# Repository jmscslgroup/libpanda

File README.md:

# Interface library for comma.ai's USB panda.

A library that handles communication with a comma.ai Panda interface device.  Simple demos collect data from the panda (grey version) to the screen.

A tutorial for hardware setup is located here:
[https://jmscslgroup.github.io/libpanda/](https://jmscslgroup.github.io/libpanda/)

Full Raspbian-based images with ROS/libpanda preinstalled can be found here:
[https://jmscslgroup.github.io/libpanda/doc/image.md](doc/image.md)

## Dependencies:
1. Required - libusb-1.0-0-dev
2. Optional - libcurses5-dev
3. Included - NMEAParser from https://github.com/visualgps/NMEAParser/

### libusb-1.0-0-dev
The core of this library is based on libusb, the default version installable through Ubuntu's apt-get.

### libcurses5-dev
An optional example for data visualization is based on ncurses.  If desired to run this example, libcurses needs to be installed but is not required

### NMEAParser
The NMEAParser is already included as a modified version with some bug fixes and added features.
1. Bugs fixed:
* Incomplete time precision for seconds in RMC strings
* Year calculation incorrect byte offset resulting in incorrect year parsings
2. Additional features:
* ZDA NMEA message parsing

## Setup:
These instructions were successful on a Raspberry pi 4 running Ubuntu 18.04.
### Install libusb-1.0-0-dev
`$ sudo apt-get install libusb-1.0-0-dev`

### Optional: install libsurses5-dev
`$ sudo apt-get install libncurses5-dev`

### Compile
1. `$ mkdir build`
2. `$ cd build`
3. `$ cmake ..`
4. `$ make`

## Examples
### simplecan
Minimal example showing a minimal implementation of classes Panda::Usb and Panda::Can (no GPS).

`$ sudo ./simplecan`

### simplegps
Minimal example showing a minimal implementation of classes Panda::Usb and Panda::Gps (no CAN).

`$ sudo ./simplegps`

### panda
Barebones example showing a minimal implementation of class Panda::Handler, utilizing Panda::Usb, Panda::Can, and Panda::Gps.  Command line arguments can be specified to record log files.

Simple Execution:

`$ sudo ./panda`

Saving CSV CAN data to file:

`$ sudo ./panda -c csvData.txt`

Saving GPS NMEA data to file, and also run USB in synchronous mode:

`$ sudo ./panda -u s -g nmeaStrings.txt`

Saving GPS NMEA, CSV CAN, and raw CAN data simultaneously:

`$ sudo ./panda -c csvData.txt -g nmeaStrings.txt -r rawCANdata.txt`

### pandaSetTime
This example listens to the GPS and when data is valid, synchronizes the system clock to the GPS's UTC if the difference is larger than a defined delta.

`$ sudo ./pandaSetTime`

### pandaCurses
An example that plots GPS and CAN data to the console in a pretty fashion.  This also takes arguments for various data collection and hardware modes.

`$ sudo ./pandaCurses`

Save NMEA strings to a file named nmeaFile.txt:

`$ sudo ./pandaCurses -g nmeaFile.txt`

Run with USB in synchronous mode (default is asynchronous):

`$ sudo ./pandaCurses -u s`

Run with faked CAN data (i.e. when not connected to a car...):

`$ sudo ./pandaCurses -f`

## Documentation:
The library is self-documenting using Doxygen, producing both HTML and LaTex.  Generate the documentation as follows:

`$ doxygen doxygen.conf`

If you do not have doxyen, you may install using, on Ubuntu:

`$ sudo apt-get install doxygen`

Or on macOS with macports:

`$ sudo port install doxygen`

## Todo
- [x] Panda GPS interface
- [ ] Isochronous USB transfer
- [ ] Timestamped libusb error logging
- [x] CAN frame parsing
- [x] CAN frame handling
- [ ] ROS based publishing
- [ ] Testing

# LICENSE

> Author: Matt Bunting
> Copyright (c) 2021 Arizona Board of Regents
> All rights reserved.
> Permission is hereby granted, without written agreement and without
> license or royalty fees, to use, copy, modify, and distribute this
> software and its documentation for any purpose, provided that the
> above copyright notice and the following two paragraphs appear in
> all copies of this software.

> IN NO EVENT SHALL THE ARIZONA BOARD OF REGENTS BE LIABLE TO ANY PARTY
> FOR DIRECT, INDIRECT, SPECIAL, INCIDENTAL, OR CONSEQUENTIAL DAMAGES
> ARISING OUT OF THE USE OF THIS SOFTWARE AND ITS DOCUMENTATION, EVEN
> IF THE UNIVERSITY OF CALIFORNIA HAS BEEN ADVISED OF THE POSSIBILITY OF
> SUCH DAMAGE.
> THE ARIZONA BOARD OF REGENTS SPECIFICALLY DISCLAIMS ANY WARRANTIES,
> INCLUDING, BUT NOT LIMITED TO, THE IMPLIED WARRANTIES OF MERCHANTABILITY
> AND FITNESS FOR A PARTICULAR PURPOSE. THE SOFTWARE PROVIDED HEREUNDER
> IS ON AN "AS IS" BASIS, AND THE UNIVERSITY OF CALIFORNIA HAS NO OBLIGATION
> TO PROVIDE MAINTENANCE, SUPPORT, UPDATES, ENHANCEMENTS, OR MODIFICATIONS.

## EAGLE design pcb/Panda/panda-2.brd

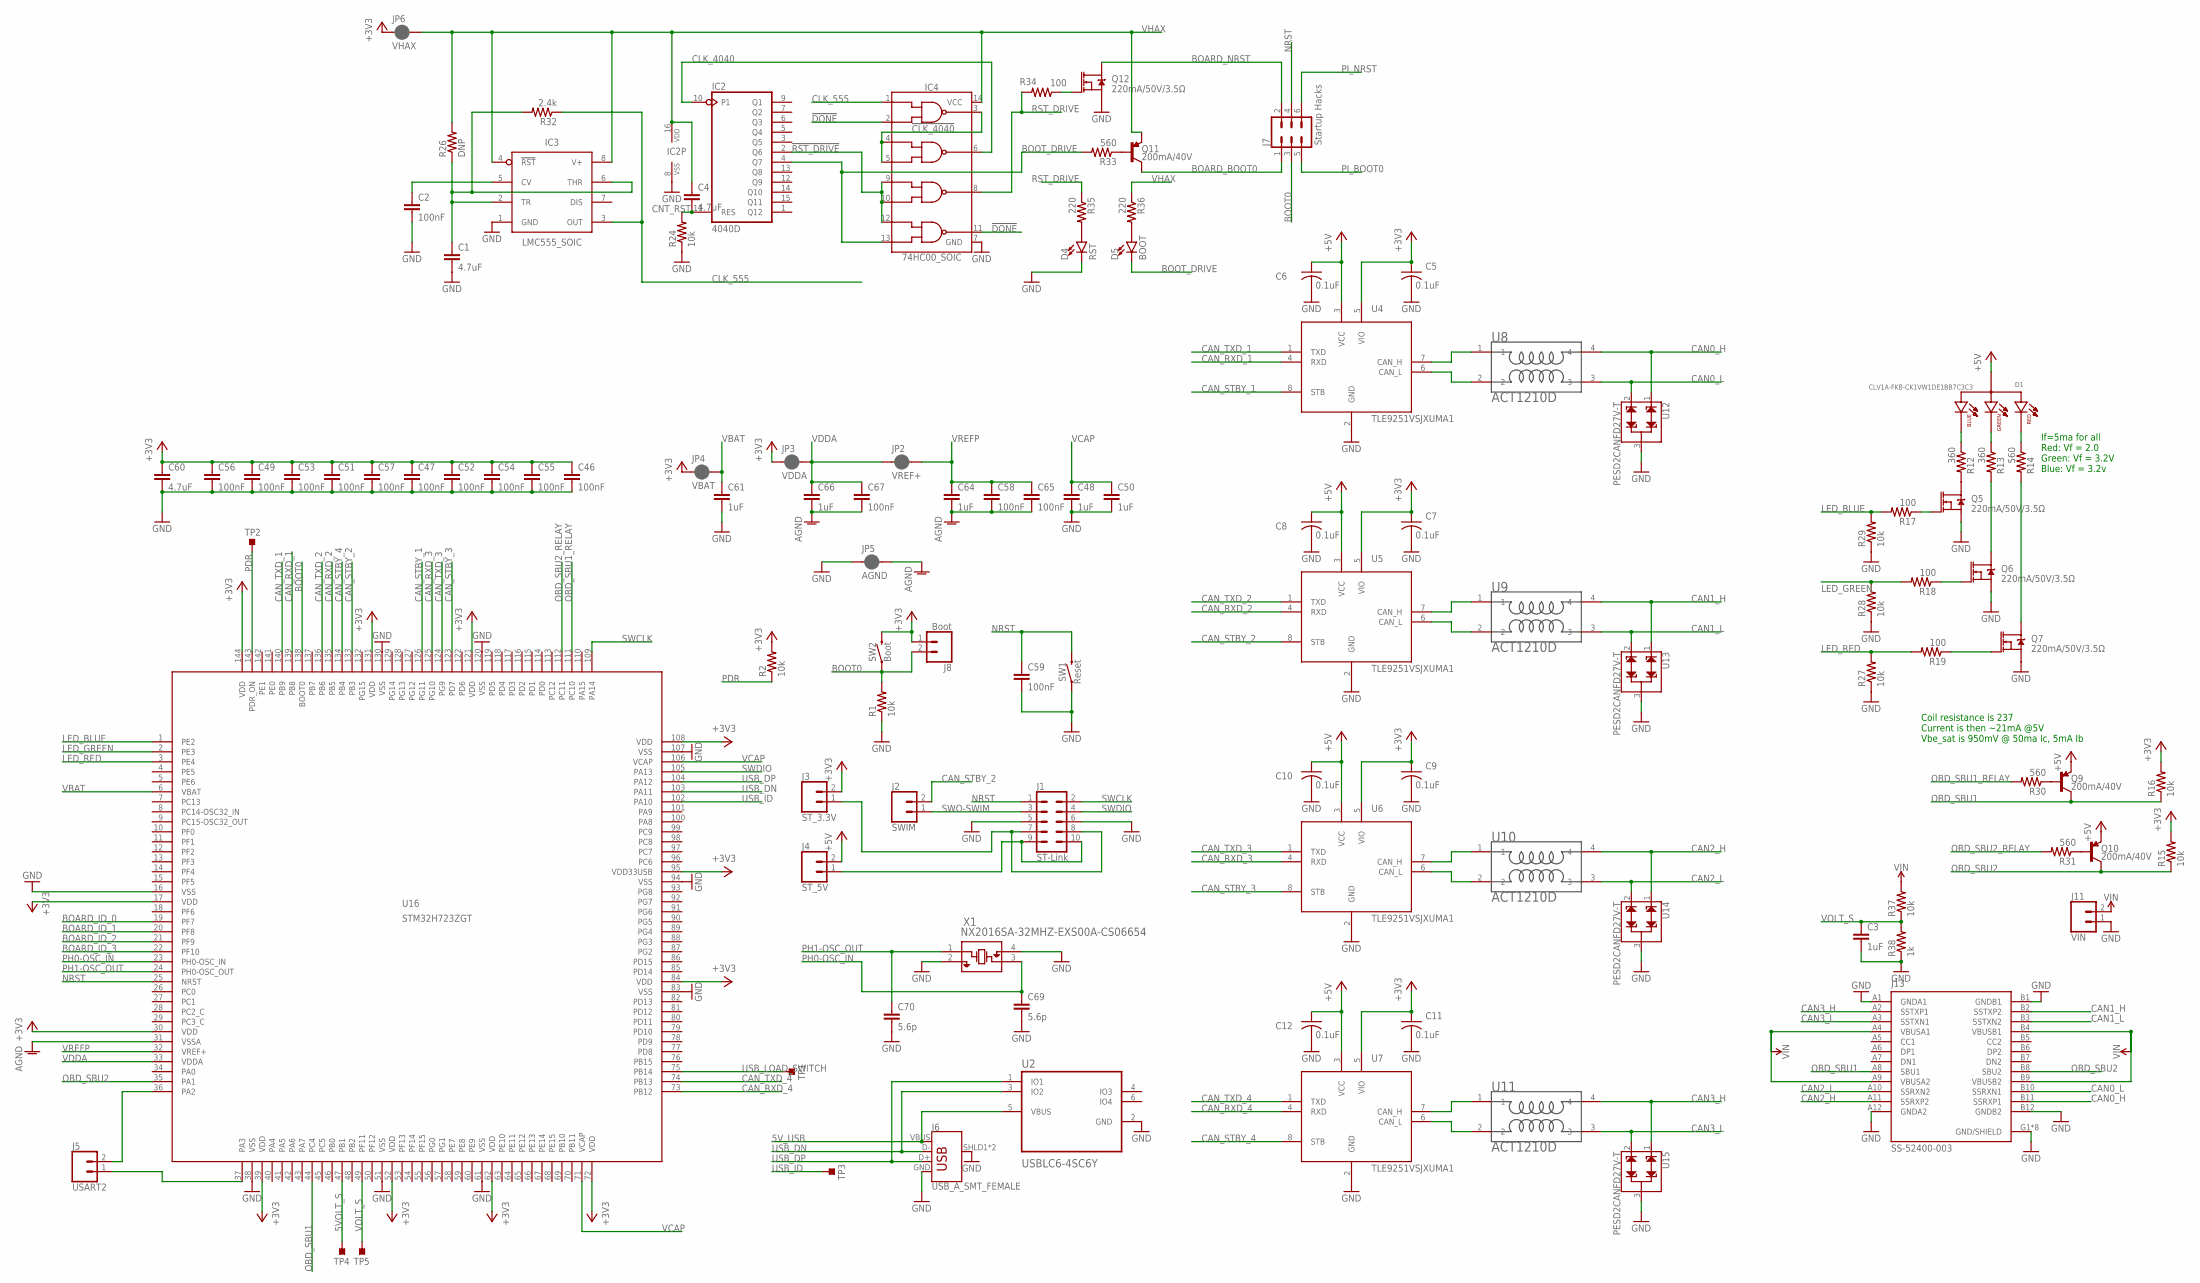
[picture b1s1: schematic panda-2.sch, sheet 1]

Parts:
C1, C4, C60: 4.7uF; C0603
C2, C46, C47, C49, C51, C52, C53, C54, C55, C56, C57, C58, C59, C65, C67: 100nF; C0402
C3, C48, C50, C61, C64, C66: 1uF; C0402
C5, C6, C7, C8, C9, C10, C11, C12: 0.1uF; C0402
C69, C70: 5.6p; C0402
D1: CLV1A-FKB-CK1VW1DE1BB7C3C3; LED_CLV1A-FKB-CK1VW1DE1BB7C3C3
D4: RST; LED-0603
D5: BOOT; LED-0603
IC2: 4040D; SO16
IC3: LMC555_SOIC; SOIC127P599X175-8N
IC4: 74HC00_SOIC; SOIC127P600X175-14N
J1: ST-Link; 2X5-SHROUDED-NS
J2: SWIM; 1X02
J3: ST_3.3V; 1X02
J4: ST_5V; 1X02
J5: USART2; 1X02
J6: USB_A_SMT_FEMALE; USB-A-S-SILK-FEMALE
J7: Startup Hacks; 2X3
J8: Boot; 1X02
J11: VIN; 1X02
J13: SS-52400-003; BELFUSE_SS-52400-003
JP2: VREF+; SMT-JUMPER_2_NC_PASTE_SILK
JP3: VDDA; SMT-JUMPER_2_NC_PASTE_SILK
JP4: VBAT; SMT-JUMPER_2_NC_PASTE_SILK
JP5: AGND; SMT-JUMPER_2_NC_PASTE_SILK
JP6: VHAX; SMT-JUMPER_2_NC_PASTE_SILK
Q5, Q6, Q7, Q12: 220mA/50V/3.5Ω; SOT23-3
Q9, Q10, Q11: 200mA/40V; SOT23-3
R1, R2, R15, R16, R24, R27, R28, R29, R37: 10k; R0402
R12, R13: 360; R0402
R14, R30, R31, R33: 560; R0402
R17, R18, R19, R34: 100; R0402
R26: DNP; R0402
R32: 2.4k; R0402
R35, R36: 220; R0402
R38: 1k; R0402
SW1: Reset; TACTILE_SWITCH_PTH_6.0MM
SW2: Boot; TACTILE_SWITCH_PTH_6.0MM
TP1: USB_LOAD_SWITCH; TESTPOINT_SMD-10SN
TP2: PDR_ON; TESTPOINT_SMD-10SN
TP3: USB_ID; TESTPOINT_SMD-10SN
TP4: 5VOUT_S; TESTPOINT_SMD-10SN
TP5: VOLT_S; TESTPOINT_SMD-10SN
U2: USBLC6-4SC6Y; SOT95P280X145-6N
U4, U5, U6, U7: TLE9251VSJXUMA1; SOIC8
U8, U9, U10, U11: ACT1210D; ACT1210-101-2P-TL
U12, U13, U14, U15: PESD2CANFD27V-T; DBZ_R-PDSO-G3
U16: STM32H723ZGT; LQFP-144
X1: NX2016SA-32MHZ-EXS00A-CS06654; NX2016SA_NDK

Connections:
5VOLT_S: TP4.TP, U16.47 (PB1)
5V_USB: J6.VBUS, U2.5 (VBUS); also elsewhere on the board
!CLK_4040: IC4.3 (1Y), IC4.4 (2A), IC4.5 (2B)
!DONE: IC4.2 (1B), IC4.11 (4Y)
!RST_DRIVE: IC2.2 (Q6), IC4.9 (3A), IC4.10 (3B), IC4.12 (4A)
+3V3: C5.1, C7.1, C9.1, C11.1, C46.1, C47.1, C49.1, C51.1, C52.1, C53.1, C54.1, C55.1, C56.1, C57.1, C60.1, J3.2, J8.1, JP3.1, JP4.1, JP6.1, R2.2, R15.2, R16.2, SW2.3 (2), U4.5 (VIO), U5.5 (VIO), U6.5 (VIO), U7.5 (VIO), U16.17 (VDD), U16.30 (VDD), U16.39 (VDD), U16.52 (VDD), U16.62 (VDD), U16.72 (VDD), U16.84 (VDD), U16.95 (VDD33USB), U16.108 (VDD), U16.121 (VDD), U16.131 (VDD), U16.144 (VDD); also elsewhere on the board
+5V: C6.1, C8.1, C10.1, C12.1, D1.2 (A), J4.2, Q9.2 (E), Q10.2 (E), U4.3 (VCC), U5.3 (VCC), U6.3 (VCC), U7.3 (VCC); also elsewhere on the board
AGND: C58.2, C64.2, C65.2, C66.2, C67.2, JP5.2, U16.31 (VSSA)
BOARD_BOOT0: J7.1, Q11.3 (C)
BOARD_ID_0: U16.19 (PF7)
BOARD_ID_1: U16.20 (PF8)
BOARD_ID_2: U16.21 (PF9)
BOARD_ID_3: U16.22 (PF10)
BOARD_NRST: J7.2, Q12.3 (D)
BOOT0: J7.3, J8.2, R1.2, SW2.1, U16.138 (BOOT0)
BOOT_DRIVE: D5.C, IC2.4 (Q7), IC4.13 (4B), R33.2
CAN0_H: J13.B11 (SSRXP1), U8.4, U12.1
CAN0_L: J13.B10 (SSRXN1), U8.3, U12.2
CAN1_H: J13.B2 (SSTXP2), U9.4, U13.1
CAN1_L: J13.B3 (SSTXN2), U9.3, U13.2
CAN2_H: J13.A11 (SSRXP2), U10.4, U14.1
CAN2_L: J13.A10 (SSRXN2), U10.3, U14.2
CAN3_H: J13.A2 (SSTXP1), U11.4, U15.1
CAN3_L: J13.A3 (SSTXN1), U11.3, U15.2
CAN_RXD_1: U4.4 (RXD), U16.139 (PB8)
CAN_RXD_2: U5.4 (RXD), U16.135 (PB5)
CAN_RXD_3: U6.4 (RXD), U16.125 (PG10)
CAN_RXD_4: U7.4 (RXD), U16.73 (PB12)
CAN_STBY_1: U4.8 (STB), U16.126 (PG11)
CAN_STBY_2: J2.2, U5.8 (STB), U16.133 (PB3)
CAN_STBY_3: U6.8 (STB), U16.123 (PD7)
CAN_STBY_4: U7.8 (STB), U16.134 (PB4)
CAN_TXD_1: U4.1 (TXD), U16.140 (PB9)
CAN_TXD_2: U5.1 (TXD), U16.136 (PB6)
CAN_TXD_3: U6.1 (TXD), U16.124 (PG9)
CAN_TXD_4: U7.1 (TXD), U16.74 (PB13)
CLK_555: IC3.3 (OUT), IC4.1 (1A), R32.1
CLK_4040: IC2.10 (P1), IC4.6 (2Y)
CNT_RST: C4.2, IC2.11 (RES), R24.2
GND: C1.2, C2.2, C3.2, C5.2, C6.2, C7.2, C8.2, C9.2, C10.2, C11.2, C12.2, C46.2, C47.2, C48.2, C49.2, C50.2, C51.2, C52.2, C53.2, C54.2, C55.2, C56.2, C57.2, C59.2, C60.2, C61.2, C69.2, C70.2, D4.C, IC2.8 (VSS), IC3.1 (GND), IC4.7 (GND), J1.5, J1.6, J6.GND, J6.SHLD1 (SHIELD), J6.SHLD2 (SHIELD), J11.1, J13.A1 (GNDA1), J13.A12 (GNDA2), J13.B1 (GNDB1), J13.B12 (GNDB2), J13.G1 (GND/SHIELD), J13.G2 (GND/SHIELD), J13.G3 (GND/SHIELD), J13.G4 (GND/SHIELD), J13.S1 (GND/SHIELD), J13.S2 (GND/SHIELD), J13.S3 (GND/SHIELD), J13.S4 (GND/SHIELD), JP5.1, Q5.2 (S), Q6.2 (S), Q7.2 (S), Q12.2 (S), R1.1, R24.1, R27.1, R28.1, R29.1, R38.1, SW1.1, U2.2 (GND), U4.2 (GND), U5.2 (GND), U6.2 (GND), U7.2 (GND), U12.3, U13.3, U14.3, U15.3, U16.16 (VSS), U16.38 (VSS), U16.51 (VSS), U16.61 (VSS), U16.83 (VSS), U16.94 (VSS), U16.107 (VSS), U16.120 (VSS), U16.130 (VSS), X1.2, X1.4; also elsewhere on the board
LED_BLUE: R17.2, R29.2, U16.1 (PE2)
LED_GREEN: R18.2, R28.2, U16.2 (PE3)
LED_RED: R19.2, R27.2, U16.3 (PE4)
unnamed: U4.7 (CAN_H), U8.1
unnamed: U4.6 (CAN_L), U8.2
unnamed: U5.7 (CAN_H), U9.1
unnamed: U5.6 (CAN_L), U9.2
unnamed: U6.7 (CAN_H), U10.1
unnamed: U6.6 (CAN_L), U10.2
unnamed: U7.7 (CAN_H), U11.1
unnamed: U7.6 (CAN_L), U11.2
unnamed: J1.7, J1.8, J3.1
unnamed: J1.9, J1.10, J4.1
unnamed: Q5.3 (D), R12.2
unnamed: D1.3 (B_C), R12.1
unnamed: D1.4 (G_C), R13.1
unnamed: D1.1 (R_C), R14.1
unnamed: Q6.3 (D), R13.2
unnamed: Q7.3 (D), R14.2
unnamed: Q9.1 (B), R30.1
unnamed: Q5.1 (G), R17.1
unnamed: Q6.1 (G), R18.1
unnamed: Q7.1 (G), R19.1
unnamed: D4.A, R35.2
unnamed: D5.A, R36.2
unnamed: J5.2, U16.36 (PA2)
unnamed: J5.1, U16.37 (PA3)
unnamed: Q10.1 (B), R31.1
unnamed: C1.1, IC3.2 (TR), IC3.6 (THR), R26.1, R32.2
unnamed: C2.1, IC3.5 (CV)
unnamed: Q11.1 (B), R33.1
unnamed: Q12.1 (G), R34.1
NRST: C59.1, J1.1, J7.4, SW1.3 (2), U16.25 (NRST)
OBD_SBU1: J13.A8 (SBU1), Q9.3 (C), R16.1, U16.44 (PC4)
OBD_SBU1_RELAY: R30.2, U16.111 (PC10)
OBD_SBU2: J13.B8 (SBU2), Q10.3 (C), R15.1, U16.35 (PA1)
OBD_SBU2_RELAY: R31.2, U16.112 (PC11)
PDR: R2.1, TP2.TP, U16.143 (PDR_ON)
PH0-OSC_IN: C69.1, U16.23 (PH0-OSC_IN), X1.3
PH1-OSC_OUT: C70.1, U16.24 (PH0-OSC_OUT), X1.1
PI_BOOT0: J7.5; also elsewhere on the board
PI_NRST: J7.6; also elsewhere on the board
RST_DRIVE: IC4.8 (3Y), R34.2, R35.1
SWCLK: J1.2, U16.109 (PA14)
SWDIO: J1.4, U16.105 (PA13)
SWO-SWIM: J1.3, J2.1
USB_DN: J6.D-, U2.3 (IO2), U16.103 (PA11)
USB_DP: J6.D+, U2.1 (IO1), U16.104 (PA12)
USB_ID: TP3.TP, U16.102 (PA10)
USB_LOAD_SWITCH: TP1.TP, U16.75 (PB14)
VBAT: C61.1, JP4.2, U16.6 (VBAT)
VCAP: C48.1, C50.1, U16.71 (VCAP), U16.106 (VCAP)
VDDA: C66.1, C67.1, JP2.1, JP3.2, U16.33 (VDDA)
VHAX: C4.1, IC2.16 (VDD), IC3.4 (!RST), IC3.8 (V+), IC4.14 (VCC), JP6.2, Q11.2 (E), R26.2, R36.1
VIN: J11.2, J13.A4 (VBUSA1), J13.A9 (VBUSA2), J13.B4 (VBUSB1), J13.B9 (VBUSB2), R37.2
VOLT_S: C3.1, R37.1, R38.2, TP5.TP, U16.49 (PF11)
VREFP: C58.1, C64.1, C65.1, JP2.2, U16.32 (VREF+)

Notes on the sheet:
If=5ma for all Red: Vf = 2.0 Green: Vf = 3.2V Blue: Vf = 3.2v
Coil resistance is 237 Current is then ~21mA @5V Vbe_sat is 950mV @ 50ma Ic, 5mA Ib

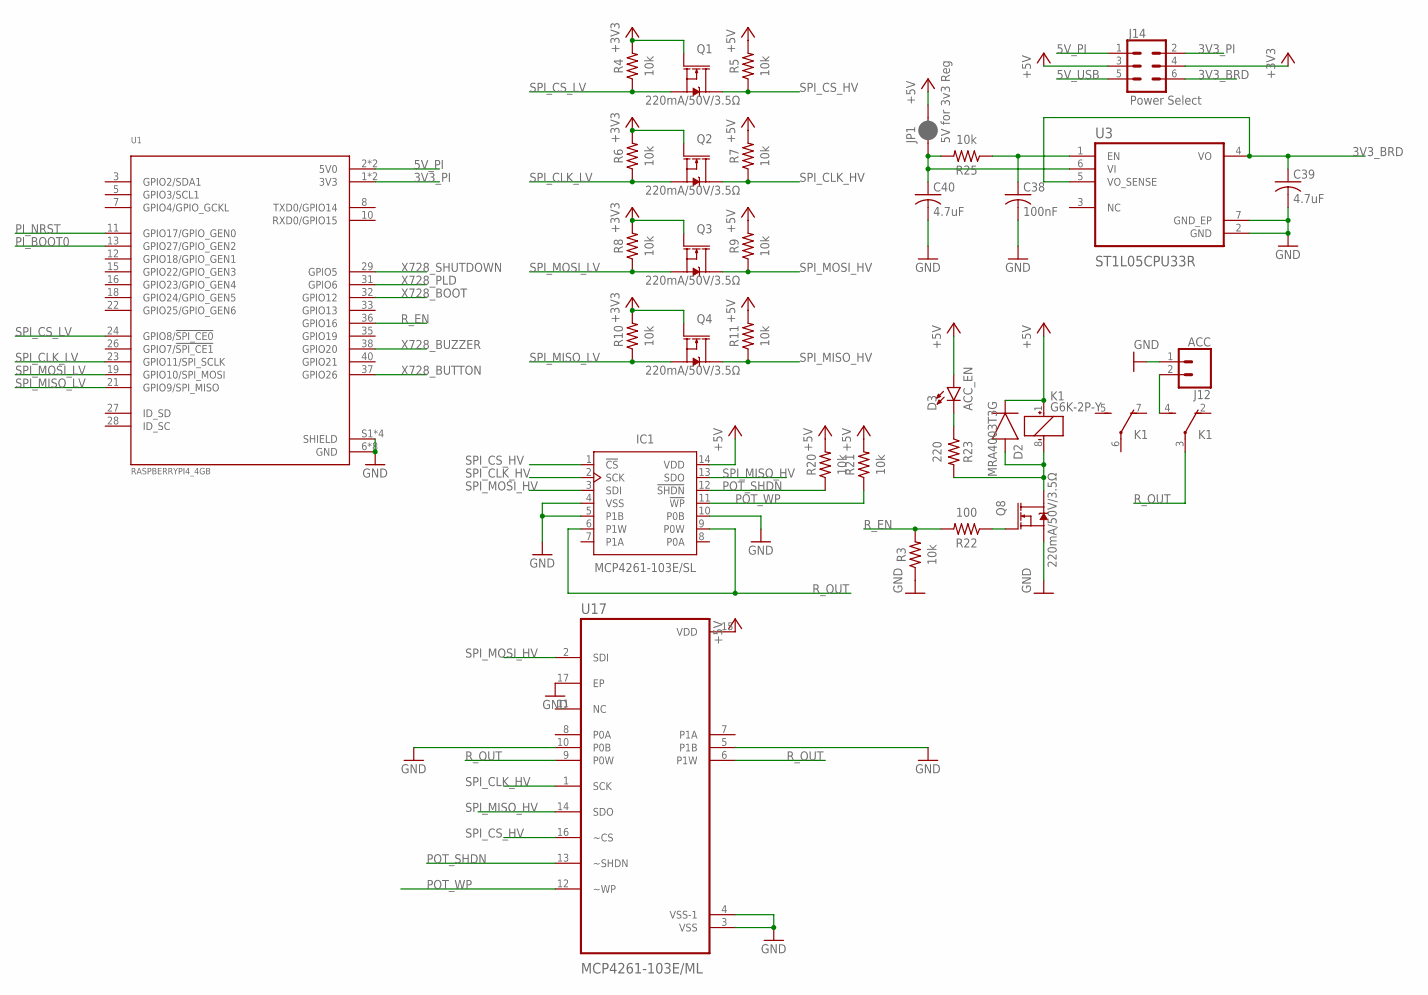
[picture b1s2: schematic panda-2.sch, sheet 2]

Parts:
C38: 100nF; CAPC1005X60
C39, C40: 4.7uF; CAPC1608X85
D2: MRA4003T3G; DIOM5226X290N
D3: ACC_EN; LED-0603
IC1: MCP4261-103E/SL; SOIC127P600X175-14N
J12: ACC; SCREWTERMINAL-5MM-2
J14: Power Select; 2X3
JP1: 5V for 3v3 Reg; SMT-JUMPER_2_NC_PASTE_SILK
K1: G6K-2P-Y
Q1, Q2, Q3, Q4, Q8: 220mA/50V/3.5Ω; SOT23-3
R3, R4, R5, R6, R7, R8, R9, R10, R11, R20, R21, R25: 10k; RESC1005X40
R22: 100; RESC1005X40
R23: 220; RESC1005X40
U1: RASPBERRYPI4_4GB; MODULE_RASPBERRYPI4_4GB
U3: ST1L05CPU33R; SON95P300X300X100-7N
U17: MCP4261-103E/ML; QFN65P400X400X100-17N

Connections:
3V3_BRD: C39.1, J14.6, U3.4 (VO), U3.5 (VO_SENSE)
3V3_PI: J14.2, U1.1 (3V3), U1.17 (3V3)
5V_PI: J14.1, U1.2 (5V0), U1.4 (5V0)
5V_USB: J14.5; also elsewhere on the board
+3V3: J14.4, Q1.1 (G), Q2.1 (G), Q3.1 (G), Q4.1 (G), R4.2, R6.2, R8.2, R10.2; also elsewhere on the board
+5V: D2.1 (C), D3.A, IC1.14 (VDD), J14.3, JP1.2, K1.1 (+), R5.2, R7.2, R9.2, R11.2, R20.2, R21.2, U17.15 (VDD); also elsewhere on the board
GND: C38.2, C39.2, C40.2, IC1.4 (VSS), IC1.5 (P1B), IC1.10 (P0B), J12.1, Q8.2 (S), R3.1, U1.6 (GND), U1.9 (GND), U1.14 (GND), U1.20 (GND), U1.25 (GND), U1.30 (GND), U1.34 (GND), U1.39 (GND), U1.S1 (SHIELD), U1.S2 (SHIELD), U1.S3 (SHIELD), U1.S4 (SHIELD), U3.2 (GND), U3.7 (GND_EP), U17.3 (VSS), U17.4 (VSS-1), U17.5 (P1B), U17.10 (P0B), U17.17 (EP); also elsewhere on the board
unnamed: J12.2, K1.4 (S)
unnamed: D3.C, R23.1
unnamed: D2.2 (A), K1.8 (-), Q8.3 (D), R23.2
unnamed: Q8.1 (G), R22.1
unnamed: C38.1, R25.1, U3.1 (EN)
unnamed: C40.1, JP1.1, R25.2, U3.6 (VI)
PI_BOOT0: U1.13 (GPIO27/GPIO_GEN2); also elsewhere on the board
PI_NRST: U1.11 (GPIO17/GPIO_GEN0); also elsewhere on the board
POT_SHDN: IC1.12 (!SHDN), R20.1, U17.13 (~SHDN)
POT_WP: IC1.11 (!WP), R21.1, U17.12 (~WP)
R_EN: R3.2, R22.2, U1.36 (GPIO16)
R_OUT: IC1.6 (P1W), IC1.9 (P0W), K1.3, U17.6 (P1W), U17.9 (P0W)
SPI_CLK_HV: IC1.2 (SCK), Q2.3 (D), R7.1, U17.1 (SCK)
SPI_CLK_LV: Q2.2 (S), R6.1, U1.23 (GPIO11/SPI_SCLK)
SPI_CS_HV: IC1.1 (!CS), Q1.3 (D), R5.1, U17.16 (~CS)
SPI_CS_LV: Q1.2 (S), R4.1, U1.24 (GPIO8/!SPI_CE0!)
SPI_MISO_HV: IC1.13 (SDO), Q4.3 (D), R11.1, U17.14 (SDO)
SPI_MISO_LV: Q4.2 (S), R10.1, U1.21 (GPIO9/SPI_MISO)
SPI_MOSI_HV: IC1.3 (SDI), Q3.3 (D), R9.1, U17.2 (SDI)
SPI_MOSI_LV: Q3.2 (S), R8.1, U1.19 (GPIO10/SPI_MOSI)
X728_BOOT: U1.32 (GPIO12)
X728_BUTTON: U1.37 (GPIO26)
X728_BUZZER: U1.38 (GPIO20)
X728_PLD: U1.31 (GPIO6)
X728_SHUTDOWN: U1.29 (GPIO5)

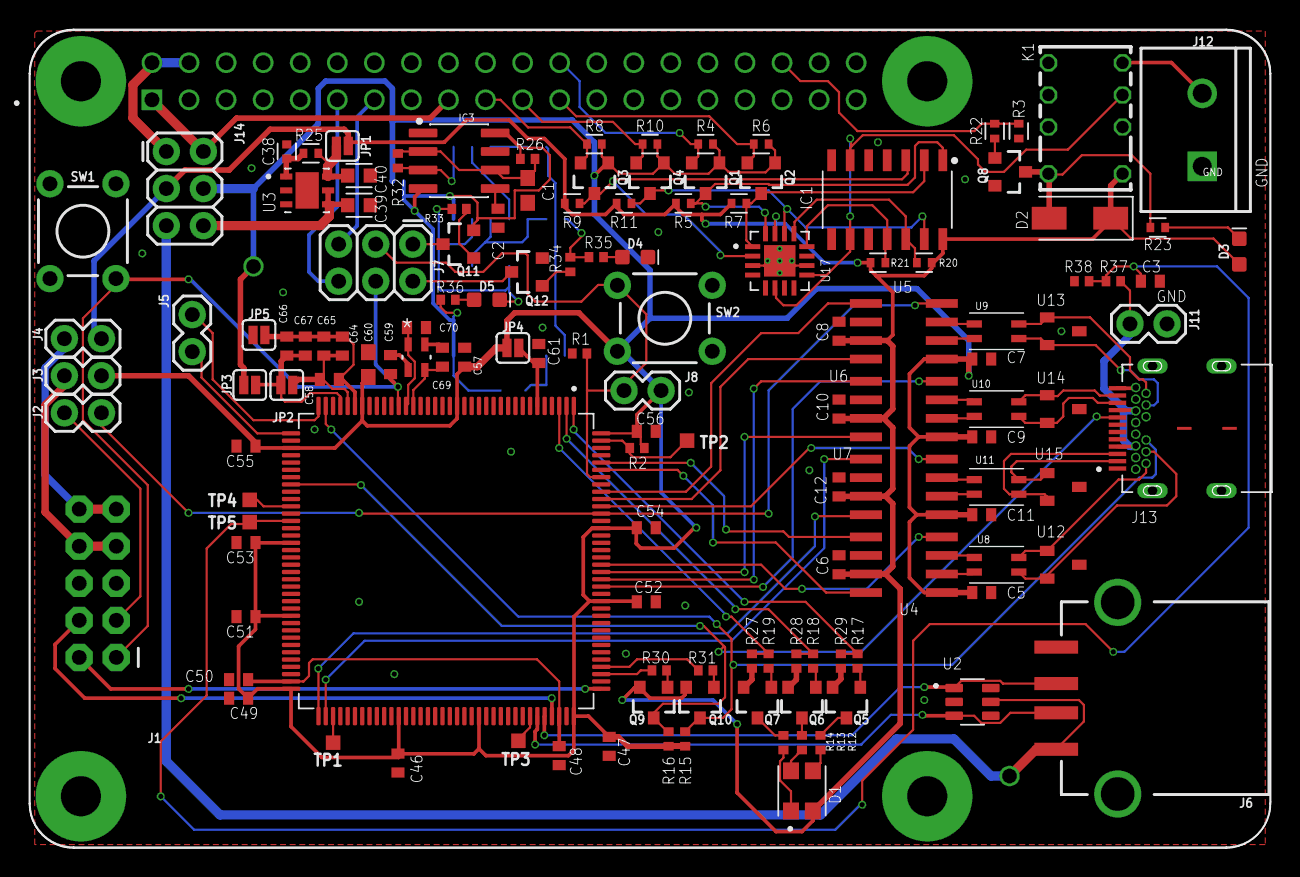
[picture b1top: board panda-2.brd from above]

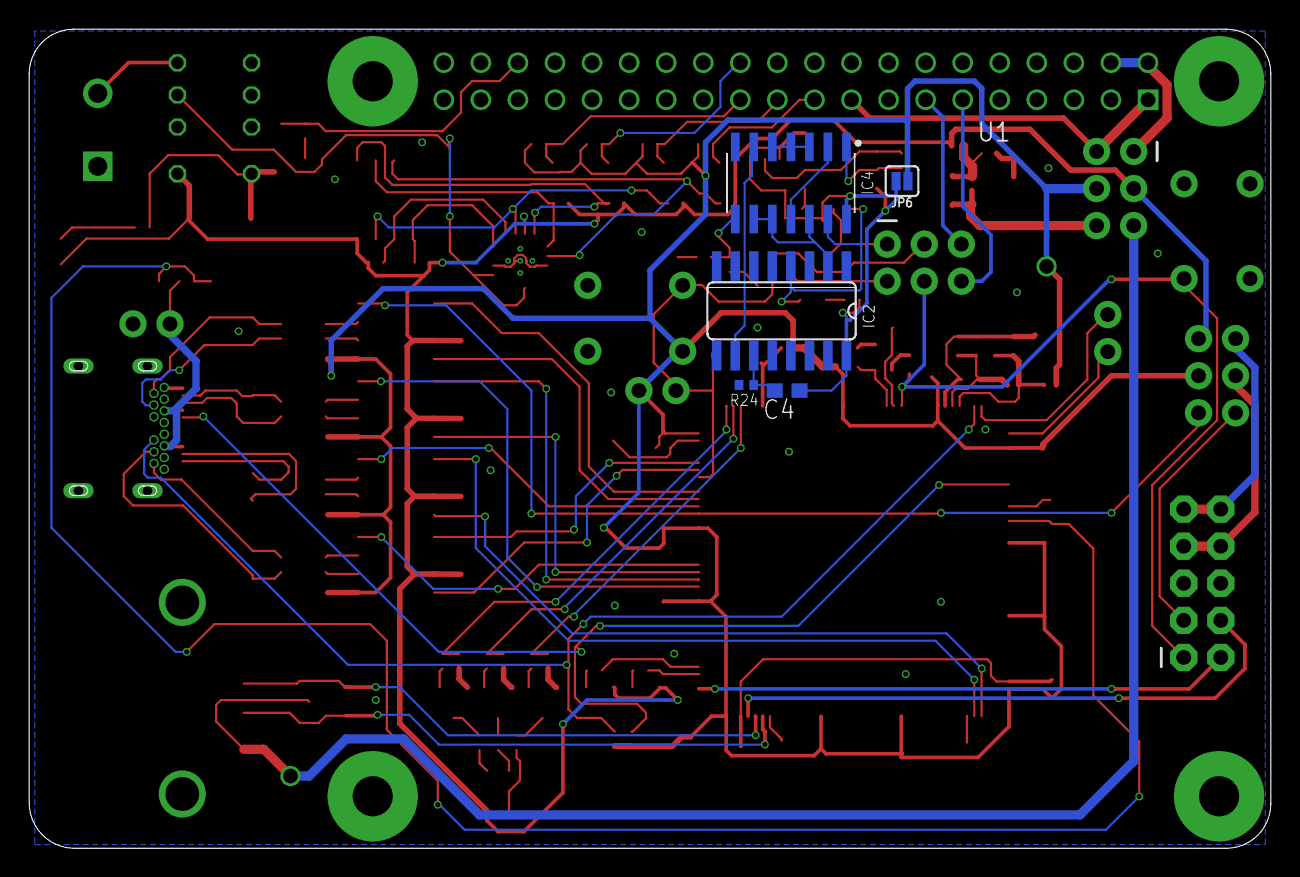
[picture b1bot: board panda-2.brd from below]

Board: 2 copper layers, 85.1 x 56.1 mm, 140 parts (6 on the bottom side), 114 nets.

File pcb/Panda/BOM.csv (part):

panda
Qty,Value,Device,Package,Parts,Link,Manufacture,Manufacturer Part Number,Description,AVAILABILITY,CATEGORY,COPYRIGHT,DESCRIPTION,FORWARD_CURRENT,MANUFACTURER,MANUFACTURER_PART_NUMBER,MF,MFR_NAME,MP,MPN,OC_FARNELL,OC_NEWARK,OPERATING_TEMP,OPERATING_TEMPERATURE,PACKAGE,PART_STATUS,POPULARITY,PRICE,PROD_ID,PURCHASE-URL,RATING,REVERSE_VOLTAGE,ROHS_COMPLIANT,SERIES,SF_ID,SF_SKU,SPICEPREFIX,SUB-CATEGORY,SUB_CATEGORY,THERMALLOSS,TOLERANCE,TYPE,VALUE,VOLTAGE_RATING,
8,0.1uF,C-USC0402,C0402,"C5, C6, C7, C8, C9, C10, C11, C12",https://www.digikey.com/en/products/detail/kyocera-avx/0402Y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,Kyocera,0402YC104KAT2A,"CAPACITOR, American symbol",,,,,,,,,,,,,,,,,,16,,,,,,,,,,C,,,,,,,,
1,100,R-US_CHIP-0402(1005-METRIC),RESC1005X40,R22,https://www.digikey.com/en/products/detail/yageo/RC0402FR-07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,YAGEO,RC0402FR-07100RL,Resistor Fixed - ANSI,,Resistor,,,,,,,,,,,,,,,,,,,,,,,,,,,Fixed,,,,,,,
3,100,R-US_R0402,R0402,"R17, R18, R19",https://www.digikey.com/en/products/detail/yageo/RC0402FR-07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,YAGEO,RC0402FR-07100RL,"RESISTOR, American symbol",,,,,,,,,,,,,,,,,,34,,,,,,,,,,R,,,,,,,,
14,100nF,C-EUC0402,C0402,"C46, C47, C49, C51, C52, C53, C54, C55, C56, C57, C58, C59, C65, C67",https://www.digikey.com/en/products/detail/kyocera-avx/0402Y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,Kyocera,0402YC104KAT2A,"CAPACITOR, European symbol",,,,,,,,,,,,,,,,,,18,,,,,,,,,,C,,,,,,,,
1,100nF,C-US_CHIP-0402(1005-METRIC),CAPC1005X60,C38,https://www.digikey.com/en/products/detail/kyocera-avx/0402Y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,Kyocera,0402YC104KAT2A,Capacitor - ANSI,,Capacitor,,,,,,,,,,,,,,,,,,,,,,,,,,,,,,,,,,
11,10k,R-US_CHIP-0402(1005-METRIC),RESC1005X40,"R4, R5, R6, R7, R8, R9, R10, R11, R20, R21, R25",https://www.digikey.com/en/products/detail/yageo/RC0402FR-07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,YAGEO,RC0402FR-0710KP,Resistor Fixed - ANSI,,Resistor,,,,,,,,,,,,,,,,,,,,,,,,,,,Fixed,,,,,,,
3,10k,R-US_R0402,R0402,"R1, R15, R16",https://www.digikey.com/en/products/detail/yageo/RC0402FR-07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,YAGEO,RC0402FR-0710KP,"RESISTOR, American symbol",,,,,,,,,,,,,,,,,,34,,,,,,,,,,R,,,,,,,,
1,150,R-US_R0402,R0402,R14,https://www.digikey.com/en/products/detail/yageo/RC0402FR-07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,YAGEO,RC0402FR-07150RL,"RESISTOR, American symbol",,,,,,,,,,,,,,,,,,34,,,,,,,,,,R,,,,,,,,
1,220,R-US_CHIP-0402(1005-METRIC),RESC1005X40,R23,https://www.digikey.com/en/products/detail/stackpole-electro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,Stackpole Electronics Inc,RES 220 OHM 5% 1/16W 0402,Resistor Fixed - ANSI,,Resistor,,,,,,,,,,,,,,,,,,,,,,,,,,,Fixed,,,,,,,
5,1uF,C-EUC0402,C0402,"C48, C50, C61, C64, C66",https://www.digikey.com/en/products/detail/kyocera-avx/04026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,Kyocera,04026C105KAT2A,"CAPACITOR, European symbol",,,,,,,,,,,,,,,,,,18,,,,,,,,,,C,,,,,,,,
8,220mA/50V/3.5Ω,MOSFET-NCH-BSS138,SOT23-3,"Q1, Q2, Q3, Q4, Q5, Q6, Q7, Q8",https://www.digikey.com/en/products/detail/onsemi/BSS138LT1G/918376,Onsemi,BSS138LT1G,N-channel MOSFETs,,,,,,,,,,,,,,,,,,,,TRANS-00830,,,,,,,,,,,,,,220mA/50V/3.5Ω,,
1,4.7uF,C-EUC0603,C0603,C60,https://www.digikey.com/en/products/detail/samsung-electro-m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,Samsung Electro-Mechanics,CL10A475KO8NNNC,"CAPACITOR, European symbol",,,,,,,,,,,,,,,,,,73,,,,,,,,,,C,,,,,,,,
2,4.7uF,C-US_CHIP-0603(1608-METRIC),CAPC1608X85,"C39, C40",https://www.digikey.com/en/products/detail/samsung-electro-m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,Samsung Electro-Mechanics,CL10A475KO8NNNC,Capacitor - ANSI,,Capacitor,,,,,,,,,,,,,,,,,,,,,,,,,,,,,,,,,,
2,5.6p,C-EUC0402,C0402,"C69, C70",https://www.digikey.com/en/products/detail/kyocera-avx/04025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,KYOCERA AVX,04025A5R6BAT2A,"CAPACITOR, European symbol",,,,,,,,,,,,,,,,,,18,,,,,,,,,,C,,,,,,,,
1,5V for 3v3 Reg,JUMPER-SMT_2_NC_PASTE_SILK,SMT-JUMPER_2_NC_PASTE_SILK,JP1,DNP,,,Normally closed solder jumper,,,,,,,,,,,,,,,,,,,,,,,,,,,,,,,,,,,,
2,90,R-US_R0402,R0402,"R12, R13",https://www.digikey.com/en/products/detail/stackpole-electro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,Stackpole Electronics Inc,RMCF0402FT88R7,"RESISTOR, American symbol",,,,,,,,,,,,,,,,,,34,,,,,,,,,,R,,,,,,,,
1,ACC,CONN_025MM,SCREWTERMINAL-5MM-2,J12,https://www.digikey.com/en/products/detail/cui-devices/TB002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,CUI Devices,TB002-500-02BE,Multi connection point. Often used as Generic Header-pin footprint for 0.1 inch spaced/style header connections,,,,,,,,,,,,,,,,,,,,,,,,,,,PRT-08432,,,,,,,,,
1,ACC_EN,LED-RED0603,LED-0603,D3,https://www.digikey.com/en/products/detail/liteon/LTST-C191K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,Lite-On Inc.,LTST-C191KRKT,Red SMD LED,,,,,,,,,,,,,,,,,,,,DIO-00819,,,,,,,,,,,,,,RED,,
4,ACT1210D,ACT1210D,ACT1210-101-2P-TL,"U8, U9, U10, U11",https://www.digikey.com/en/products/detail/tdk-corporation/A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,TDK Corporation,ACT1210D-510-2P-TL00,,,,,,,,,,,,,,,,,,,,,,,,,,,,,,,,,,,,,
1,AGND,JUMPER-SMT_2_NC_PASTE_SILK,SMT-JUMPER_2_NC_PASTE_SILK,JP5,DNP,,,Normally closed solder jumper,,,,,,,,,,,,,,,,,,,,,,,,,,,,,,,,,,,,
1,Boot,CONN_02,1X02,J8,https://www.digikey.com/en/products/detail/würth-elektronik/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,Würth Elektronik,61300211121,Multi connection point. Often used as Generic Header-pin footprint for 0.1 inch spaced/style header connections,,,,,,,,,,,,,,,,,,,,,,,,,,,,,,,,,,,,
1,CLV1A-FKB-CK1VW1DE1BB7C3C3,CLV1A-FKB-CK1VW1DE1BB7C3C3,LED_CLV1A-FKB-CK1VW1DE1BB7C3C3,D1,https://www.digikey.com/en/products/detail/creeled-inc/CLV1A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,"CreeLED, Inc.",CLV1A-FKB-CK1VW1DE1BB7C3C3,PLCC4 3 in 1 SMD LED Check availability,In Stock,,,"Red, Green, Blue (RGB) 622nm Red, 528nm Green, 468nm Blue LED Indication - Discrete 2V Red, 3.2V Green, 3.2V Blue 4-PLCC",,,,Cree Inc.,,CLV1A-FKB-CK1VW1DE1BB7C3C3,,,,,,PLCC-4 Cree Inc.,,,None,,https://pricing.snapeda.com/search/part/CLV1A-FKB-CK1VW1DE1B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,,,,,,,,,,,,,,,
1,G6K-2P-Y,G6K-2P-Y,G6K-2P-Y,K1,https://www.digikey.com/en/products/detail/omron-electronics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,Omron Electronics Inc-EMC Div,G6K-2P-Y DC3,Low Signal Relay,,,,,,,,OMRON COMPONENTS USA,,,G6K-2P-Y DC12,3937276,34C3464,,,,,0,,,,,,,,,,,,,,,,,,
1,MCP4261-103E/ML,MCP4261-103E/ML,QFN65P400X400X100-17N,U17,https://www.digikey.com/en/products/detail/microchip-technol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,,,,,,,Digital Potentiometer 10kOhm 256POS Non-Volatile Linear Automotive 16-Pin QFN EP Tube,Microchip,,MCP4261-103E/ML,,,,,,QFN-16 Microchip,,,None,,https://pricing.snapeda.com/search/part/MCP4261-103E/ML/?ref=eda,,,,,,,,,,,,,,,,1,MCP4261-103E/ML,MCP4261-103E/ML
1,MCP4261-103E/SL,MCP4261-103E/SLSOIC-14,SOIC127P600X175-14N,IC1,DNP,,,7/8-Bit Single/Dual SPI Digital POT with Volatile Memory,,IC_Data-Conversion,,,,Microchip Technology,,,,,MCP4261-103E/SL,,,,-40°C ~ 125°C,,ACTIVE,,,,,,,COMPLIANT,MCP42X,,,,,Digital Potentiometer,0.4 W,,,MCP4261-103E/SL,,
1,MRA4003T3G,DIODE_MRA4003T3G_SMA,DIOM5226X290N,D2,https://www.mouser.com/ProductDetail/onsemi/MRA4003T3G?qs=Zp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,onsemi,MRA4003T3G,Diode Rectifier - Popular parts,,Diode,,DIODE GEN PURP 300V 1A SMA,,ON Semiconductor ,,,,,,,,,,,,,,,,,,,,,,,Rectifier,,,,,MRA4003T3G,,
1,NX2016SA-32MHZ-EXS00A-CS06654,NX2016SA-32MHZ-EXS00A-CS06654,NX2016SA_NDK,X1,https://www.digikey.com/en/products/detail/ndk-america-inc/N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,"NDK America, Inc.",NX2016SA-25.000M-STD-CZS-1,,,,Copyright (C) 2022 Ultra Librarian. All rights reserved.,,,,NX2016SA-32MHZ-EXS00A-CS06654,,NDK,,,,,,,,,,,,,,,,,,,,,,,,,,,
4,PESD2CANFD27V-T,PESD2CANFD27V-T,DBZ_R-PDSO-G3,"U12, U13, U14, U15",https://www.digikey.com/en/products/detail/nexperia-usa-inc/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,Nexperia USA Inc.,PESD2CANFD27V-TR,,,,,,,,,,,,,,,,,,,,,,,,,,,,,,,,,,,,,
1,Power Select,CONN_03X2FEMALE,2X3,J14,https://www.digikey.com/en/products/detail/metz-connect-usa-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,METZ CONNECT USA Inc.,PR20203VBDN,Multi connection point. Often used as Generic Header-pin footprint for 0.1 inch spaced/style header connections,,,,,,,,,,,,,,,,,,,,CONN-11566,,,,,,,,,,,,,,FEMALE 2x3,,
1,RASPBERRYPI4_4GB,RASPBERRYPI4_4GB,MODULE_RASPBERRYPI4_4GB,U1,https://www.digikey.com/en/products/detail/samtec-inc/SSQ-12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,Samtec Inc.,SSQ-120-03-T-D,"BCM2835 Raspberry Pi Model B+ - ARM11, VideoCore MPU Embedded Evaluation Board  Check availability",In Stock,,,BCM2711 Raspberry Pi 4 Model B 4GB - ARM® Cortex®-A72 MPU Embedded Evaluation Board,,,,Raspberry Pi,,RASPBERRY PI 4B/4GB,,,,,,None,,,None,,https://pricing.snapeda.com/search/part/RASPBERRY PI 4B/4GB/?ref=eda,,,,,,,,,,,,,,,
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
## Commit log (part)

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2022-09-30 We need these now for live iewer
2022-09-30 new location
2022-09-30 fix json parsing
2022-09-30 Ugh, the uninstall piece was commented out in the committed version.
2022-10-04 adding option to update VIN without asking for user input
2022-10-06 corrected error that was not removing the previous installs
2022-10-11 adding update time to piStatus
2022-10-11 adding CPU use and fixing variable names to be accurate
2022-10-14 piStatus bug fix.
2022-10-17 Added WiringPi in installation, for SPI communication
2022-10-21 Bug fix
2022-10-24 Added pcb design and BOM
2022-10-24 Board designed with BOM, had to change 555 timer package
2022-10-25 Added install and update scripts
2022-10-27 Working buzzer test in libpanda
2022-10-27 Added a reset program for the matthat
2022-10-29 Added matthat reset function into USB initializationa and as a separate program
2022-10-29 Ensuring repo is in a compileable state, this has efforts for the new nissan acc controller but is far from finished
2022-10-30 Buzzer is now multithreaded HYPERS
2022-10-30 First working cruise with state amchine rev 2
2022-10-30 Fixed a potential memory issue tih acc butotn checking
2022-10-31 revise speed planner parsing with updated schema design
2022-11-01 fix msg types
2022-11-02 Update to type
2022-11-03 select lane-level speed plan
2022-11-03 fix defaults when speed planner is unavailble
2022-11-03 Changed naming of orange wire file to be better descriptive
2022-11-04 Quieter button presses (slightly)
2022-11-04 Better state initialization
2022-11-04 making live changes
2022-11-04 fix lane_num datatype
2022-11-04 end of live test, just moved live planner python to onnx2ros
2022-11-05 Added a check for a busy button press, for synchronous logic
2022-11-05 Added python3-rosdep
2022-11-05 uncommenting the can service robot upstart uninstall in the rl_cruise update scripts.
2022-11-05 mvt vehicle will rsync PandaData (csv for CAN and GPS) and bagfiles to mvtpi user on ransom on shutdown
2022-11-06 creating accButtonWire (name?) in /etc/libpanda.d/ in the install script
2022-11-06 Updated pi status to upload libpanda hash.
2022-11-07 atoUpdate modified to work on any internet connection (cradlepoint data will be fine). Also script will now execture the new update.sh scrips in libpanda/ so that we have an easy place to edit and te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
2022-11-07 autoUpdate now checks gih hash of libpanda before performing instlal scripts
2022-11-07 Scratch the prior commit on error logging update.sh, that didn't help. Bug fixed anyway
2022-11-07 update.sh and called install scripts now check out specific commits based on the repository hash
2022-11-07 adding log messages to scripts. adding log messages and sed checking of bad url characters.
2022-11-07 log messages added to autoupdate
2022-11-07 Changed ros package file path to be absolute
2022-11-07 rosnodeChecker will check for ROS being up first, and then rosnode down
2022-11-08 cd out of repo
2022-11-09 Added acc wire status file debug message
2022-11-09 adding vin_details.json update automatically
2022-11-10 The latest panda firmware repository has a simple script to flash our custom pi hat
2022-11-10 temp
2022-11-10 update live_tracker hash
2022-11-10 testing privs with '...'
2022-11-11 Added install and update scripts for RL cruise planner
2022-11-12 install_explicit_cruise_accel
2022-11-12 Correct can_to_ros for RL accel-based
2022-11-12 Correct algos-stack
2022-11-12 New algos-stack hash
2022-11-12 new algosstack
2022-11-12 Updated can file on rosResositories.csv
2022-11-13 New algo-stack hash
2022-11-13 Resetting to turn off stock ACC and back to working algos-stack hash
2022-11-13 Fix: error if empty arg $1
2022-11-13 Updated HEAD hashes and rosnode checker now reports whether controls are allowed.
2022-11-13 Changed algo-stack hash for bug fix.
2022-11-13 adding can to ros has with save params operational.
2022-11-14 fixing hash copy error
2022-11-14 Working hash from today with clamp
2022-11-14 include is_wb = True hardcoding for Monday
2022-11-14 Update rosRepositories.csv
    Original working code + jl_controls_allowable
2022-11-14 Publish lat and long to ROS
2022-11-14 RosNodeChecker bug fix and change to speed planner to change json files atomically.
2022-11-14 Aboudy's and Adit's Westbound changes
2022-11-14 Fied live_tracker libpanda hash to accomodate is_wb hardcoding.
2022-11-14 Hash adjustment for can_to_ros to accomodate merge from jl-ctrls-allowable
2022-11-14 publish transferred to onnx
2022-11-14 algos-stack
2022-11-15 Added cruiseRequest() and corresponding heartbeat, referenced by statemachine rev6 in slack #hardware
2022-11-15 Acc wire checking also checks external power connection. Timing adjusted to ensure power disconnect detected within CAN check range. Also hacked a way to chekc button press immediately on startup
2022-11-15 Added a time hystersis on power disconnect, now circlesmanager wiats for 1 minute before attempting to ping then upload data
2022-11-15 hard code controls allowed
2022-11-15 pre merge
2022-11-15 Change states that disarm relay to not invoke button checking logic, and renamed button press function to be more clear in its function
2022-11-15 Pre-merge hash from master
2022-11-15 Update scripts changed to allow future easier controller installs
2022-11-15 Patched Algo-stack hash to reflect changes there.
2022-11-15 adding mapping for experimental control cars to update different repo hashes
2022-11-15 pre-merge 2
2022-11-15 Updated hashes for catkin_ws.
2022-11-15 pistatus changes for rosRepo hashes
2022-11-15 Record only for standard vehicles that ar enot experimental
2022-11-16 update hashes for day3
2022-11-16 Copied repository hashes from Experimental into the normal. Also accidentally added tutorial images
2022-11-17 this is the same as Zhe's PR, but without the final new line. I also added a test script, which passes this version
2022-11-18 Removed generated file that was accidentally added
2023-01-11 Modified build scripts to compile on x86 macoss. may still work on rasbian?
2023-03-21 pandazone may work if both files are specified, but only works with default zone file. therefore only records when near campus and near testbed Tough to test
2023-03-21 Timestamps match, but theres a fun DST issue that makes it an hour off, maybe only sometimes
2023-03-27 Added polygon normal cacluation, and also polygon orientation. coming next is polygon expansion/contraction
2023-03-27 pandazone now inputs the path of data diles rather than files directly. corresponding script pandarecord.sh reflects this
2023-03-27 Fixed segfault due to heartbeat still triggering from long loop wait
2023-04-03 Added zonefile exports, for importing into privzone
2023-04-04 Fixed bluezone installation
2023-04-04 Added a status characteristic for bluezone
2023-04-05 Added wifi ap scanning
2023-04-06 pandarecord was making folders based on date, but this is now handled within pandazone
2023-04-06 Made notification counts print a new line every 100 characters in pandazone fo reasier journalctl checking
2023-04-07 Wifi remove implemented
2023-04-07 Fixed issues with utf-8 encoding between bash, python, and js
2023-04-12 Moved usbmuxd install from crazypifi to main install
2023-04-12 Install now has usbmuxd
2023-04-12 Bluezone now saves files, and can separately read procedd zonefiles
2023-04-12 Added logic to flip zone inclusion/exclusion based on hsyteresis sign
2023-04-18 Apps are now a thing. handles services whether it involves ROS or not. Reauires specific structure
2023-04-18 Removed hardcoding of /home/circles/libpanda to use src directory from location of running install.sh, also user can be dynamic
2023-04-19 pandazone now opens defualt zonefile if no custom zonefile exists
2023-04-19 bluezone now reports app status
2023-04-19 Fixed current app status when uninstalled
2023-04-19 bluezone install now restarts everyhing, incase of software update
2023-04-19 More fixes to simpleSend install
2023-04-20 App restart/stop integrated
2023-04-20 Easy fix for mutliple vuDevices getting added
2023-04-20 Bluezone now reads default zonefile if custom is not created
2023-04-21 Changed file naming scheme of csv fiels in pandazone
2023-04-21 Filling out the cbf app
2023-04-24 Changed cbf launchfile, added it to description
2023-04-24 cbf isntall script acronym error solved
2023-04-24 Fixed uninstall of and can service
2023-04-24 Aligned cbf app with new package/launch file
2023-04-25 Steering has life in the Toyota RAV4
2023-05-01 Changed Joystick to use Logitech gamepad mapping
2023-05-01 Fixed discoverable bluetooth on install
2023-05-04 Removed beep recording based on zone
2023-05-05 Autoupdate runs at vehicle shutdown, after data upload if there's internet
2023-05-05 Oops, indentation tabs/spaces issue in circles amanger fixed
2023-05-26 Update pandarecord.sh to loud recording
2023-05-30 Silent reocirding back
2023-08-01 New pi image with links
2023-08-03 adding joy_to_veh app
    Adding the joystick demo for steering and acceleration as an app. TODO: resolve ambiguity on uninstall with apps.
2023-08-04 making bash scripts for joy_to_veh app executable
2023-08-04 proper naming
2023-08-04 Cleaned cbf for calling uninstall in robot upstart in random places
2023-08-04 I did not steal this commit from M.Nice
2023-08-07 MAde the toyotaHandler class stich itself together regarding tht esteering simulator so it doe snot need to be done externally
2023-08-07 Removed extraneous vehicle_interface install for robot_upstart
2023-08-07 Whoops, cbf needs setpoint reader but package was never included
2023-08-09 Have some barebones third party app registration working
2023-08-10 Added bluezone capability to include other app repositores
2023-08-10 oops, broke app descriptions but is fixed now. also added branch verification that will automatically remove repo if branch does not exist
2023-08-11 autoUpdate now also invokes libapdan app updates
2023-08-11 Fix variable typo when checking if app to install is None
2023-08-14 Getting repo deletes, this may fix a permissions issue
2023-08-14 Fixed incorrect reporting of status if none installed
2023-08-14 Fix syntax error in app maanger
2023-08-14 oops syntax in app manager
2023-08-15 untested iCommand install script added
2023-08-17 Added new app-manifest paradigm including manifest verion checking and including current app state infirmation. Also includings methods to automatically migrate old versions ot the new structure
2023-08-17 Removed apps from libpanda to prevent confusion. See github.com/jmscslgroup/libpanda-default-apps in the future
2023-08-18 bug fix from switching to bash arrays
2023-08-21 Added helper function for git checkoouts
2023-08-22 Fixed a migration bug
2023-08-22 Added a fatal check if yq has issues
2023-08-22 Suppressing output of yq check
2023-08-25 Added app install dependency functionality for pip3 and apt. see MatthewNice/gps2vsl for example
2023-09-19 ROS install script includes tf2, tested to work on fresh raspbian images
2023-09-22 Added cantools, and also pip3 to install
2023-10-05 Some better UBX command handling with GPS modules. now things liek the covariance matrix can be polled through UBX
2023-11-13 Changed autoUpdate to be after the baseline script.
2023-12-20 changed permissions of git commands to reflect libapnda user environemnt to help out with private repository apps
2024-08-20 initial modifications for gocmd-based file sync
2024-08-22 gocmd install integrated and tested in libpanda install
2024-08-22 configuration path added for go sync
2024-08-27 removing use of ils in favor of gocmd ls
2024-09-10 adding bagfile sync functionality
2024-09-11 making sure to use gocmd only, not any icommands for listing remote file size
2024-11-06 Forgot to reference cyverse dest directory in other scripts
2025-07-24 added HARDCODED VIN to prevent ELIMINATED panda support segfault
2025-07-24 massive graph for SNR scoring

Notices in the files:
pcb/Panda/BOM.csv:
www.digikey.com/en/products/detail/ndk-america-inc/NX2016SA-25-000M-STD-CZS-1/5022956,"NDK America, Inc.",NX2016SA-25.000M-STD-CZS-1,,,,Copyright (C) 2022 Ultra Librarian. All rights reserved.,,,,NX2016SA-32MHZ-EXS00A-CS06654,,NDK,,,,,,,,,,,,,,,,,,,,,,,,,,,
parts and their libraries:
SparkFun-DiscreteSemi: Licensing: Creative Commons ShareAlike 4.0 International - https://creativecommons.org/licenses/by-sa/4.0
COPYRIGHT: Copyright (C) 2022 Ultra Librarian. All rights reserved.
